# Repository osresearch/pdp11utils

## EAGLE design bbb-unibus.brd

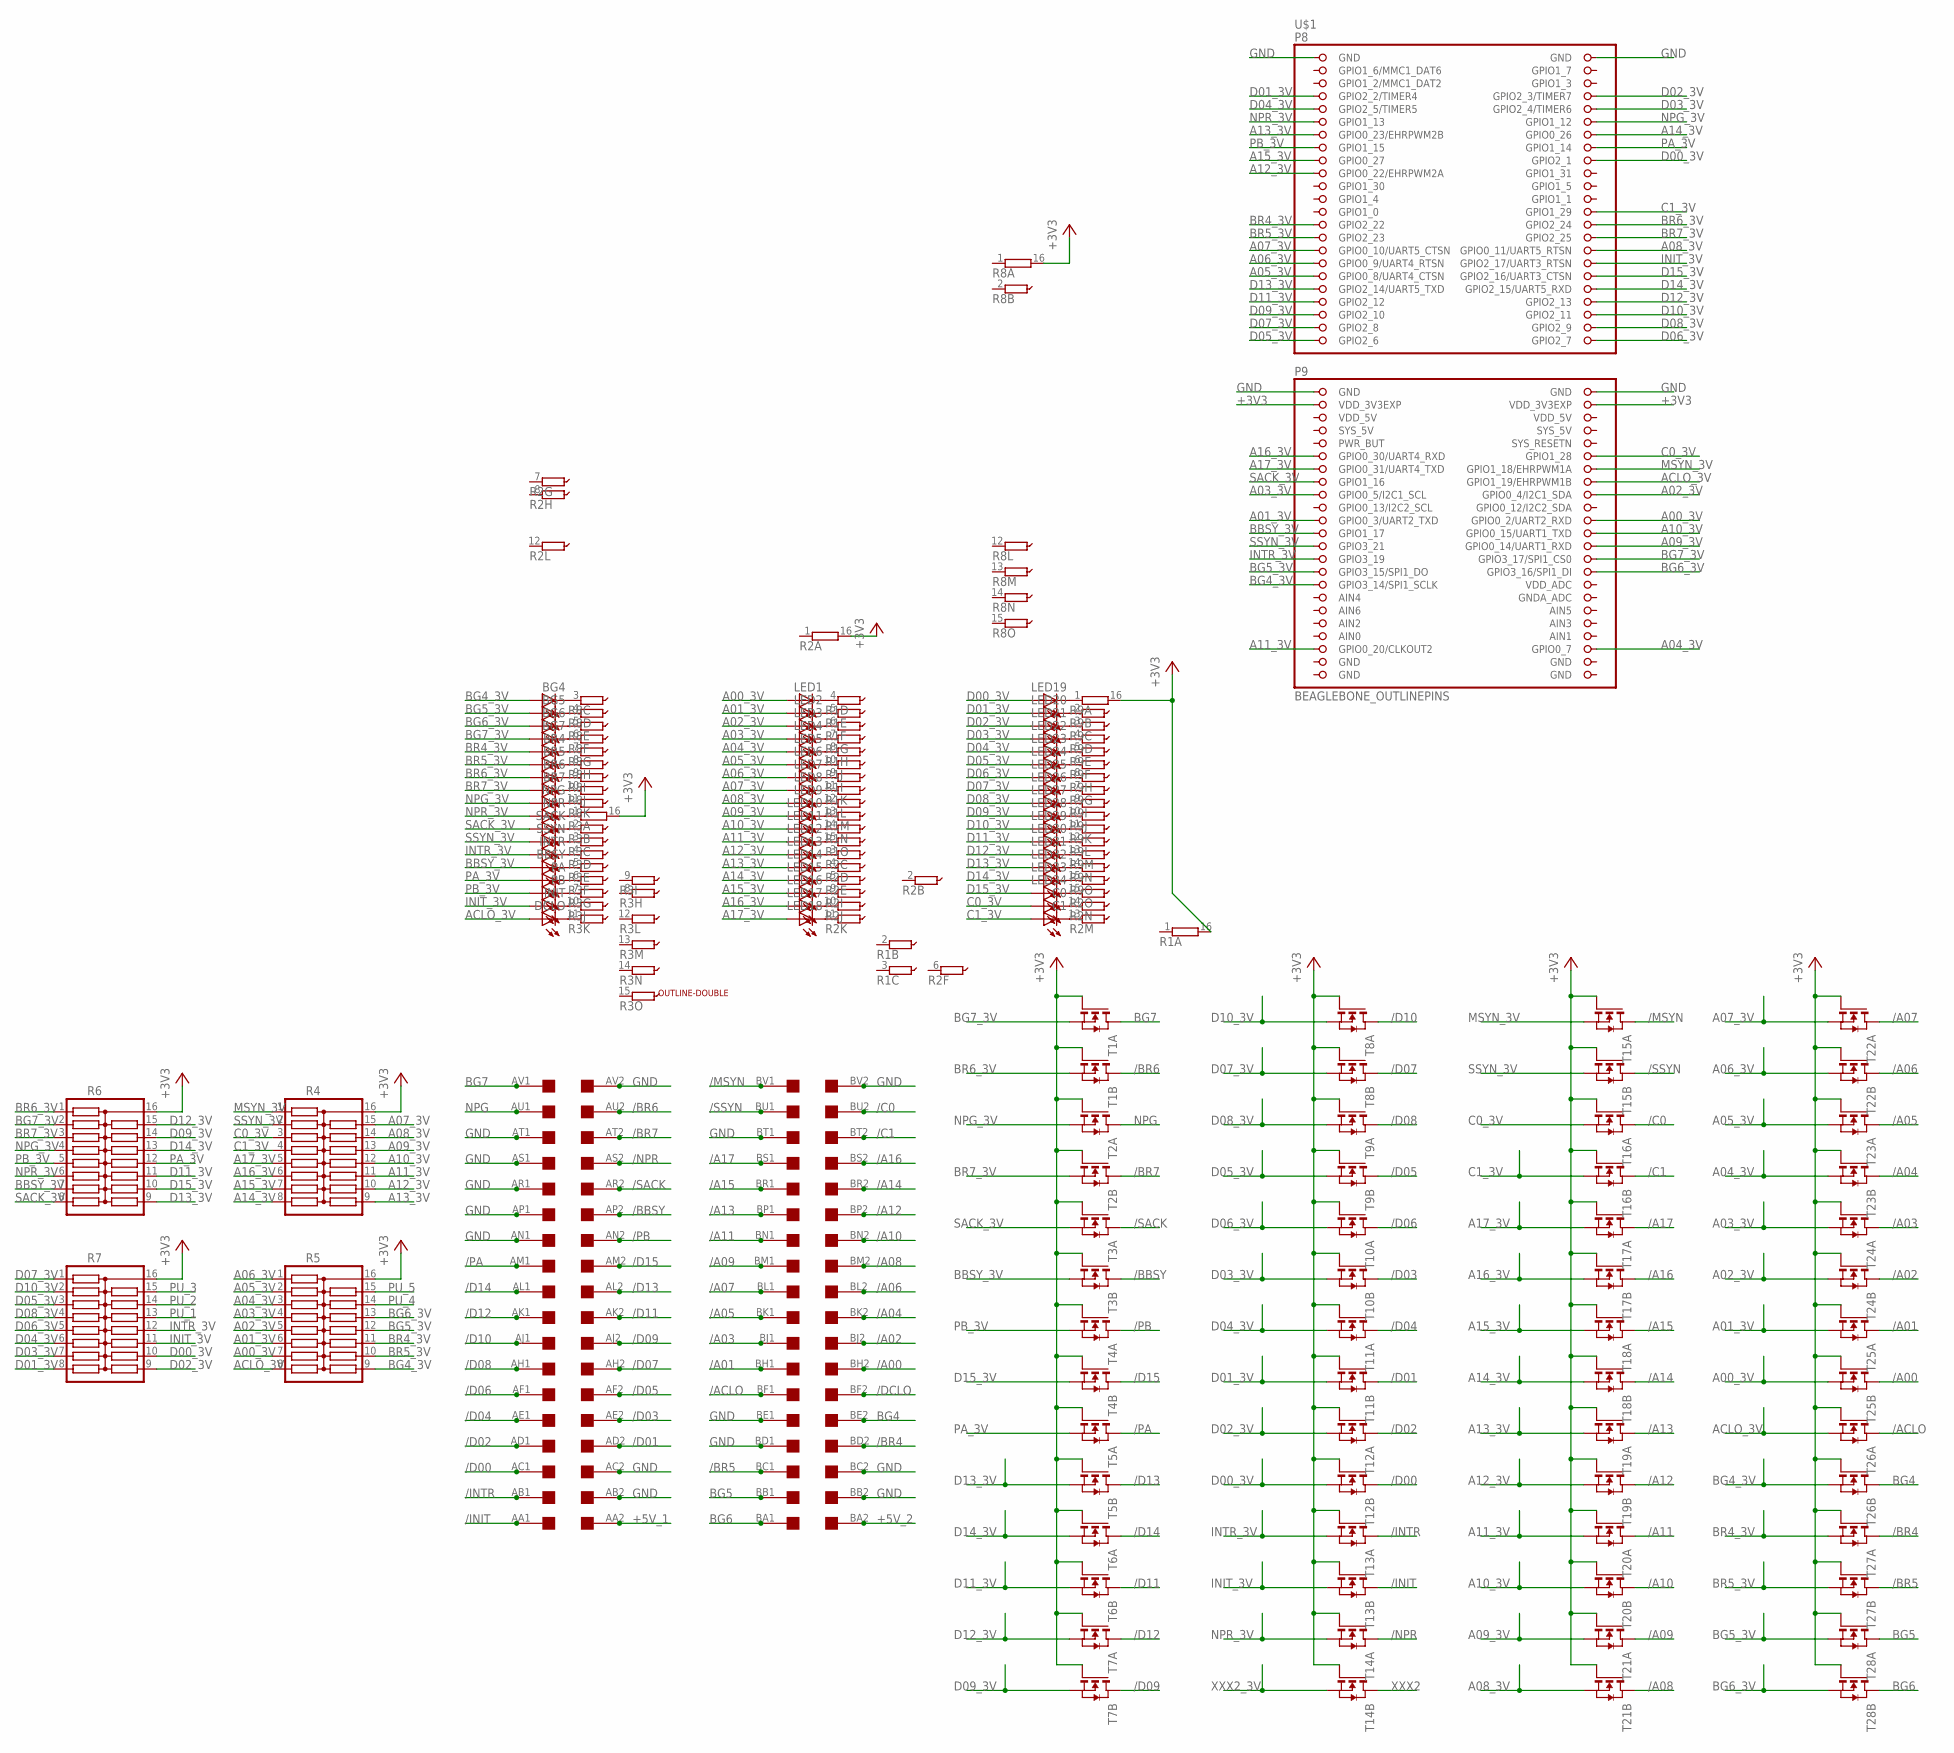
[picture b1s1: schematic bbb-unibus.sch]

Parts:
BBSY: LEDSML0805; SML0805
BG4, BG5, BG6, BG7: LEDSML0805; SML0805
BR4, BR5, BR6, BR7: LEDSML0805; SML0805
C0, C1: LEDSML0805; SML0805
DCLO: LEDSML0805; SML0805
INIT: LEDSML0805; SML0805
INTR: LEDSML0805; SML0805
LED1, LED2, LED3, LED4, LED5, LED6, LED7, LED8, LED9, LED10, LED11, LED12, LED13, LED14, LED15, LED16, LED17, LED18, LED19, LED20, LED21, LED22, LED23, LED24, LED25, LED26, LED27, LED28, LED29, LED30, LED31, LED32, LED33, LED34: LEDSML0805; SML0805
NPG: LEDSML0805; SML0805
NPR: LEDSML0805; SML0805
PA: LEDSML0805; SML0805
PB: LEDSML0805; SML0805
R1, R2, R3, R8, R9: 2QSP16-15E; 2QSP16
R4, R5, R6, R7: 2QSP16-15; 2QSP16
SACK: LEDSML0805; SML0805
SSYN: LEDSML0805; SML0805
T1, T2, T3, T4, T5, T6, T7, T8, T9, T10, T11, T12, T13, T14, T15, T16, T17, T18, T19, T20, T21, T22, T23, T24, T25, T26, T27, T28: NMOS2-BSS138DW; SOT363
U$1: BEAGLEBONE_OUTLINEPINS; BEAGLEBONE_PINS
U$2: OUTLINE-DOUBLE; DOUBLE
U$3: DOUBLE; EDGE-CON4

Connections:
+3V3: R1.16 (2), R2.16 (2), R3.16 (2), R4.16, R5.16, R6.16, R7.16, R8.16 (2), R9.16 (2), T1.2 (G), T1.5 (G), T2.2 (G), T2.5 (G), T3.2 (G), T3.5 (G), T4.2 (G), T4.5 (G), T5.2 (G), T5.5 (G), T6.2 (G), T6.5 (G), T7.2 (G), T7.5 (G), T8.2 (G), T8.5 (G), T9.2 (G), T9.5 (G), T10.2 (G), T10.5 (G), T11.2 (G), T11.5 (G), T12.2 (G), T12.5 (G), T13.2 (G), T13.5 (G), T14.2 (G), T14.5 (G), T15.2 (G), T15.5 (G), T16.2 (G), T16.5 (G), T17.2 (G), T17.5 (G), T18.2 (G), T18.5 (G), T19.2 (G), T19.5 (G), T20.2 (G), T20.5 (G), T21.2 (G), T21.5 (G), T22.2 (G), T22.5 (G), T23.2 (G), T23.5 (G), T24.2 (G), T24.5 (G), T25.2 (G), T25.5 (G), T26.2 (G), T26.5 (G), T27.2 (G), T27.5 (G), T28.2 (G), T28.5 (G), U$1.49 (VDD_3V3EXP), U$1.50 (VDD_3V3EXP)
+5V_1: U$3.AA2
+5V_2: U$3.BA2
/A00: T25.6 (D), U$3.BH2
/A01: T25.3 (D), U$3.BH1
/A02: T24.6 (D), U$3.BJ2
/A03: T24.3 (D), U$3.BJ1
/A04: T23.6 (D), U$3.BK2
/A05: T23.3 (D), U$3.BK1
/A06: T22.6 (D), U$3.BL2
/A07: T22.3 (D), U$3.BL1
/A08: T21.6 (D), U$3.BM2
/A09: T21.3 (D), U$3.BM1
/A10: T20.6 (D), U$3.BN2
/A11: T20.3 (D), U$3.BN1
/A12: T19.6 (D), U$3.BP2
/A13: T19.3 (D), U$3.BP1
/A14: T18.6 (D), U$3.BR2
/A15: T18.3 (D), U$3.BR1
/A16: T17.6 (D), U$3.BS2
/A17: T17.3 (D), U$3.BS1
/ACLO: T26.3 (D), U$3.BF1
/BBSY: T3.6 (D), U$3.AP2
/BR4: T27.3 (D), U$3.BD2
/BR5: T27.6 (D), U$3.BC1
/BR6: T1.6 (D), U$3.AU2
/BR7: T2.6 (D), U$3.AT2
/C0: T16.3 (D), U$3.BU2
/C1: T16.6 (D), U$3.BT2
/D00: T12.6 (D), U$3.AC1
/D01: T11.6 (D), U$3.AD2
/D02: T12.3 (D), U$3.AD1
/D03: T10.6 (D), U$3.AE2
/D04: T11.3 (D), U$3.AE1
/D05: T9.6 (D), U$3.AF2
/D06: T10.3 (D), U$3.AF1
/D07: T8.6 (D), U$3.AH2
/D08: T9.3 (D), U$3.AH1
/D09: T7.6 (D), U$3.AJ2
/D10: T8.3 (D), U$3.AJ1
/D11: T6.6 (D), U$3.AK2
/D12: T7.3 (D), U$3.AK1
/D13: T5.6 (D), U$3.AL2
/D14: T6.3 (D), U$3.AL1
/D15: T4.6 (D), U$3.AM2
/DCLO: U$3.BF2
/INIT: T13.6 (D), U$3.AA1
/INTR: T13.3 (D), U$3.AB1
/MSYN: T15.3 (D), U$3.BV1
/NPR: T14.3 (D), U$3.AS2
/PA: T5.3 (D), U$3.AM1
/PB: T4.3 (D), U$3.AN2
/SACK: T3.3 (D), U$3.AR2
/SSYN: T15.6 (D), U$3.BU1
A00_3V: LED1.A, R5.7, T25.4 (S), U$1.68 (GPIO0_2/UART2_RXD)
A01_3V: LED2.A, R5.6, T25.1 (S), U$1.67 (GPIO0_3/UART2_TXD)
A02_3V: LED3.A, R5.5, T24.4 (S), U$1.64 (GPIO0_4/I2C1_SDA)
A03_3V: LED4.A, R5.4, T24.1 (S), U$1.63 (GPIO0_5/I2C1_SCL)
A04_3V: LED5.A, R5.3, T23.4 (S), U$1.88 (GPIO0_7)
A05_3V: LED6.A, R5.2, T23.1 (S), U$1.35 (GPIO0_8/UART4_CTSN)
A06_3V: LED7.A, R5.1, T22.4 (S), U$1.33 (GPIO0_9/UART4_RTSN)
A07_3V: LED8.A, R4.15, T22.1 (S), U$1.31 (GPIO0_10/UART5_CTSN)
A08_3V: LED9.A, R4.14, T21.4 (S), U$1.32 (GPIO0_11/UART5_RTSN)
A09_3V: LED10.A, R4.13, T21.1 (S), U$1.72 (GPIO0_14/UART1_RXD)
A10_3V: LED11.A, R4.12, T20.4 (S), U$1.70 (GPIO0_15/UART1_TXD)
A11_3V: LED12.A, R4.11, T20.1 (S), U$1.87 (GPIO0_20/CLKOUT2)
A12_3V: LED13.A, R4.10, T19.4 (S), U$1.19 (GPIO0_22/EHRPWM2A)
A13_3V: LED14.A, R4.9, T19.1 (S), U$1.13 (GPIO0_23/EHRPWM2B)
A14_3V: LED15.A, R4.8, T18.4 (S), U$1.14 (GPIO0_26)
A15_3V: LED16.A, R4.7, T18.1 (S), U$1.17 (GPIO0_27)
A16_3V: LED17.A, R4.6, T17.4 (S), U$1.57 (GPIO0_30/UART4_RXD)
A17_3V: LED18.A, R4.5, T17.1 (S), U$1.59 (GPIO0_31/UART4_TXD)
ACLO_3V: DCLO.A, R5.8, T26.1 (S), U$1.62 (GPIO1_19/EHRPWM1B)
AIN0: U$1.85 (AIN0)
BBSY_3V: BBSY.A, R6.7, T3.4 (S), U$1.69 (GPIO1_17)
BG4: T26.6 (D), U$3.BE2
BG4_3V: BG4.A, R5.9, T26.4 (S), U$1.77 (GPIO3_14/SPI1_SCLK)
BG5: T28.3 (D), U$3.BB1
BG5_3V: BG5.A, R5.12, T28.1 (S), U$1.75 (GPIO3_15/SPI1_DO)
BG6: T28.6 (D), U$3.BA1
BG6_3V: BG6.A, R5.13, T28.4 (S), U$1.76 (GPIO3_16/SPI1_DI)
BG7: T1.3 (D), U$3.AV1
BG7_3V: BG7.A, R6.2, T1.1 (S), U$1.74 (GPIO3_17/SPI1_CS0)
BR4_3V: BR4.A, R5.11, T27.1 (S), U$1.27 (GPIO2_22)
BR5_3V: BR5.A, R5.10, T27.4 (S), U$1.29 (GPIO2_23)
BR6_3V: BR6.A, R6.1, T1.4 (S), U$1.28 (GPIO2_24)
BR7_3V: BR7.A, R6.3, T2.4 (S), U$1.30 (GPIO2_25)
C0_3V: C0.A, R4.3, T16.1 (S), U$1.58 (GPIO1_28)
C1_3V: C1.A, R4.4, T16.4 (S), U$1.26 (GPIO1_29)
D00_3V: LED19.A, R7.10, T12.4 (S), U$1.18 (GPIO2_1)
D01_3V: LED20.A, R7.8, T11.4 (S), U$1.7 (GPIO2_2/TIMER4)
D02_3V: LED21.A, R7.9, T12.1 (S), U$1.8 (GPIO2_3/TIMER7)
D03_3V: LED22.A, R7.7, T10.4 (S), U$1.10 (GPIO2_4/TIMER6)
D04_3V: LED23.A, R7.6, T11.1 (S), U$1.9 (GPIO2_5/TIMER5)
D05_3V: LED24.A, R7.3, T9.4 (S), U$1.45 (GPIO2_6)
D06_3V: LED25.A, R7.5, T10.1 (S), U$1.46 (GPIO2_7)
D07_3V: LED26.A, R7.1, T8.4 (S), U$1.43 (GPIO2_8)
D08_3V: LED27.A, R7.4, T9.1 (S), U$1.44 (GPIO2_9)
D09_3V: LED28.A, R6.14, T7.4 (S), U$1.41 (GPIO2_10)
D10_3V: LED29.A, R7.2, T8.1 (S), U$1.42 (GPIO2_11)
D11_3V: LED30.A, R6.11, T6.4 (S), U$1.39 (GPIO2_12)
D12_3V: LED31.A, R6.15, T7.1 (S), U$1.40 (GPIO2_13)
D13_3V: LED32.A, R6.9, T5.4 (S), U$1.37 (GPIO2_14/UART5_TXD)
D14_3V: LED33.A, R6.13, T6.1 (S), U$1.38 (GPIO2_15/UART5_RXD)
D15_3V: LED34.A, R6.10, T4.4 (S), U$1.36 (GPIO2_16/UART3_CTSN)
GND: U$1.1 (GND), U$1.2 (GND), U$1.47 (GND), U$1.48 (GND), U$3.AB2, U$3.AC2, U$3.AN1, U$3.AP1, U$3.AR1, U$3.AS1, U$3.AT1, U$3.AV2, U$3.BB2, U$3.BC2, U$3.BD1, U$3.BE1, U$3.BT1, U$3.BV2
INIT_3V: INIT.A, R7.11, T13.4 (S), U$1.34 (GPIO2_17/UART3_RTSN)
INTR_3V: INTR.A, R7.12, T13.1 (S), U$1.73 (GPIO3_19)
MSYN_3V: R4.1, T15.1 (S), U$1.60 (GPIO1_18/EHRPWM1A)
unnamed: LED34.C, R2.15 (1)
unnamed: C0.C, R2.14 (1)
unnamed: C1.C, R2.13 (1)
unnamed: LED16.C, R2.9 (1)
unnamed: LED1.C, R1.4 (1)
unnamed: LED2.C, R1.5 (1)
unnamed: LED3.C, R1.6 (1)
unnamed: LED4.C, R1.7 (1)
unnamed: LED5.C, R1.8 (1)
unnamed: LED6.C, R1.10 (1)
unnamed: LED7.C, R1.9 (1)
unnamed: LED8.C, R1.11 (1)
unnamed: LED9.C, R1.12 (1)
unnamed: LED10.C, R1.13 (1)
unnamed: LED11.C, R1.14 (1)
unnamed: LED12.C, R1.15 (1)
unnamed: LED13.C, R2.3 (1)
unnamed: LED17.C, R2.10 (1)
unnamed: LED18.C, R2.11 (1)
unnamed: LED14.C, R2.4 (1)
unnamed: LED15.C, R2.5 (1)
unnamed: BR5.C, R8.8 (1)
unnamed: BR4.C, R8.7 (1)
unnamed: BG7.C, R8.6 (1)
unnamed: BG6.C, R8.5 (1)
unnamed: BG5.C, R8.4 (1)
unnamed: BG4.C, R8.3 (1)
unnamed: BR6.C, R8.9 (1)
unnamed: BR7.C, R8.10 (1)
unnamed: NPG.C, R8.11 (1)
unnamed: LED26.C, R9.7 (1)
unnamed: NPR.C, R3.1
unnamed: LED25.C, R9.8 (1)
unnamed: R3.2 (1), SACK.C
unnamed: R3.3 (1), SSYN.C
unnamed: INTR.C, R3.4 (1)
unnamed: LED19.C, R9.1
unnamed: LED20.C, R9.2 (1)
unnamed: LED21.C, R9.3 (1)
unnamed: LED22.C, R9.4 (1)
unnamed: LED23.C, R9.5 (1)
unnamed: LED24.C, R9.6 (1)
unnamed: LED27.C, R9.9 (1)
unnamed: LED28.C, R9.10 (1)
unnamed: LED29.C, R9.11 (1)
unnamed: LED30.C, R9.12 (1)
unnamed: LED31.C, R9.13 (1)
unnamed: LED32.C, R9.14 (1)
unnamed: LED33.C, R9.15 (1)
unnamed: BBSY.C, R3.5 (1)
unnamed: PA.C, R3.6 (1)
unnamed: PB.C, R3.7 (1)
unnamed: INIT.C, R3.10 (1)
unnamed: DCLO.C, R3.11 (1)
NPG: T2.3 (D), U$3.AU1
NPG_3V: NPG.A, R6.4, T2.1 (S), U$1.12 (GPIO1_12)
NPR_3V: NPR.A, R6.6, T14.1 (S), U$1.11 (GPIO1_13)
PA_3V: PA.A, R6.12, T5.1 (S), U$1.16 (GPIO1_14)
PB_3V: PB.A, R6.5, T4.1 (S), U$1.15 (GPIO1_15)
PU_1: R7.13
PU_2: R7.14
PU_3: R7.15
PU_4: R5.14
PU_5: R5.15
SACK_3V: R6.8, SACK.A, T3.1 (S), U$1.61 (GPIO1_16)
SSYN_3V: R4.2, SSYN.A, T15.4 (S), U$1.71 (GPIO3_21)
SYS_5V: U$1.53 (SYS_5V)
UNUSED_GND0: U$1.89 (GND)
UNUSED_GND1: U$1.91 (GND)
UNUSED_GND2: U$1.90 (GND)
UNUSED_GND3: U$1.92 (GND)
VDD_5V: U$1.51 (VDD_5V), U$1.52 (VDD_5V)
XXX2: T14.6 (D)
XXX2_3V: T14.4 (S)

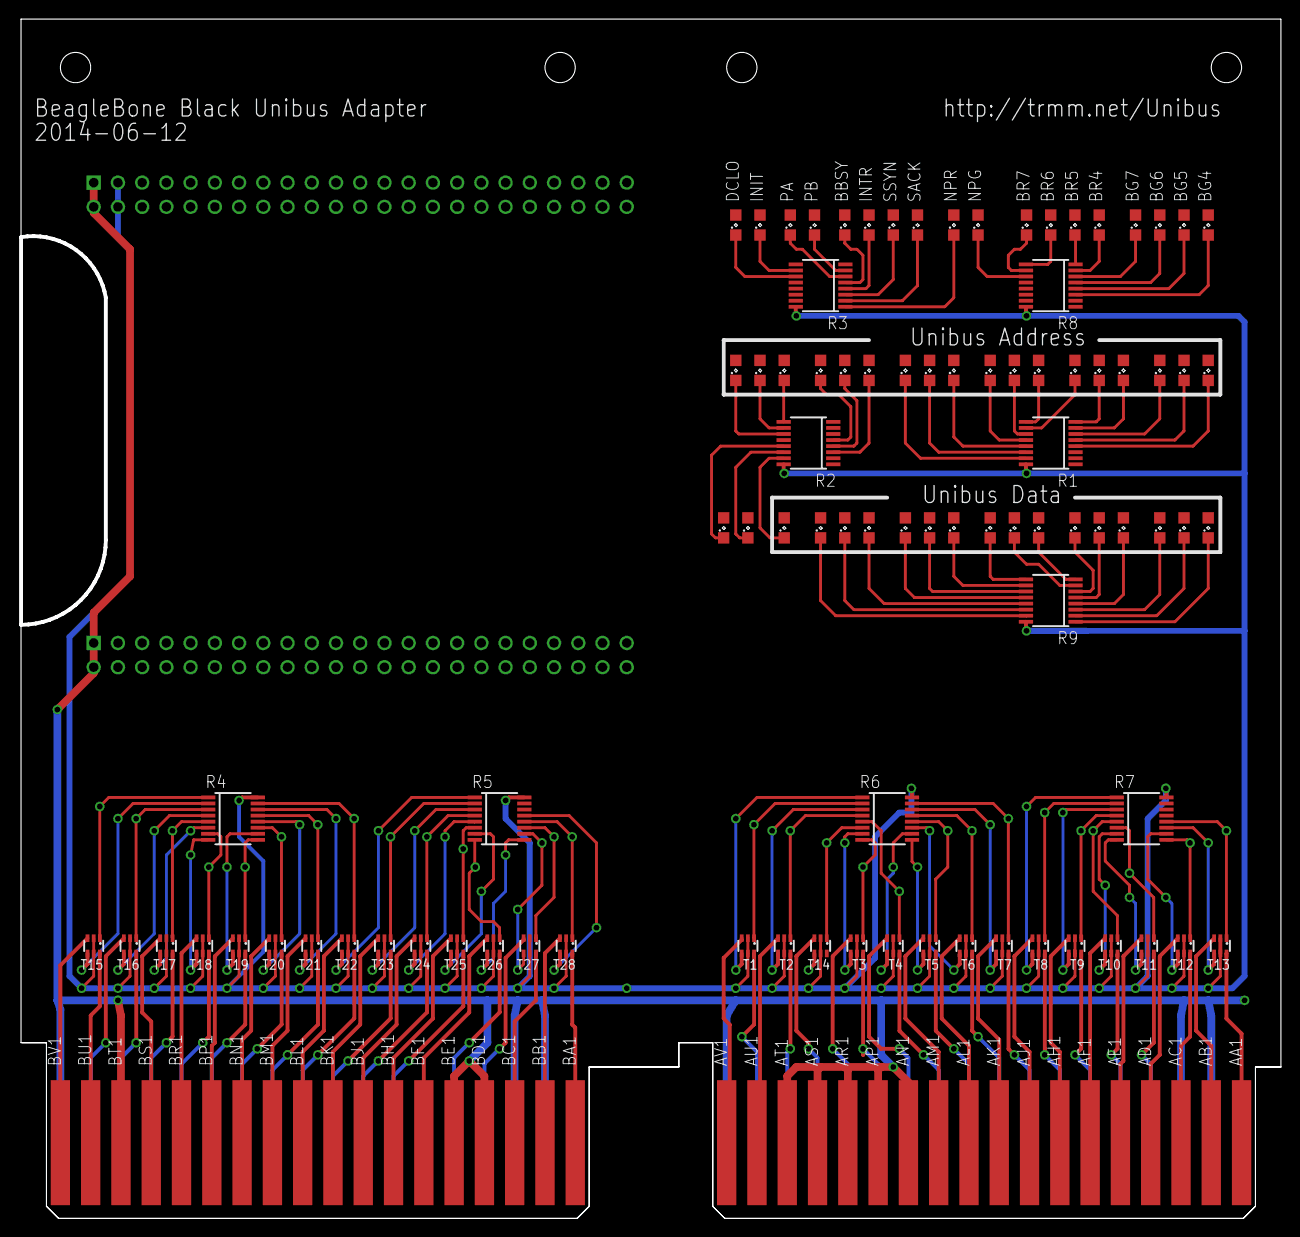
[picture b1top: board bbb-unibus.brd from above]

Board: 2 copper layers, 131.9 x 125.3 mm, 94 parts (1 on the bottom side), 167 nets.

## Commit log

2014-06-13 BeagleBone Black Unibus adapter (unrouted)
2014-06-13 slowly feed files over the serial port to EDIT/CREATE
2014-06-13 text
2014-06-13 vector font
2014-06-13 import of digital logo
2014-06-13 use 200dpi import rather than 1000 for logo
2014-06-28 started on unibus monitoring code for BeagleBone black
2014-06-28 bit extraction routines
2014-06-28 lots of gpio fixes; need a makefile
2014-06-28 renamed
2014-06-28 makefile builds
2014-06-28 pinmux
2014-06-29 use pinmux offsets. why, TI?
2014-06-29 Overlay file
2014-06-29 try writing to pinmux
2014-06-29 enable pullups
2014-06-29 fix offset of pins
2014-06-29 negative shifts are not right
2014-06-29 silence startup
2014-06-29 fix addres bit ranges
2014-06-29 output all the bits
2014-06-29 include gpio3.14
2014-06-29 P9.31 for exclusive
2014-06-29 moved unibus into separate file
2014-06-29 switch back to inline macros
2014-06-29 fix u->init bit read
2014-06-29 unibus read/write and bus mastering
2014-06-29 enable debugging and check for map failure
2014-07-12 enable pullups on outputs when entering slave mode
